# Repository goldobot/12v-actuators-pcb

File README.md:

# 12v-actuators-pcb
 Carte pour les actuateurs pneumatiques + capteur, moteurs brushless, répartition 12V et arrêt d'urgence du robot l'équipe Goldorak.

## Specs composants carte actionneurs 12V
- Fuse holder keystone 3557-2
- D2PAK for p-channel mosfet ( https://fr.rs-online.com/web/p/transistors-mosfet/7105014 )
- STM32 uC: STM32F042K6 MCU sur carte de développement compatible pinout Arduino Nano
- 3 esc modules on board 15A
- 2 esc 35 off-board signal + alim, connecteur imposé
- Capteurs de pression, double emprunte
- Passer le 12V au pont en H, connecteur imposé
- Entrée NTC 100k piston compresseur -> uC
- 3 sorties électrovannes + 1 sortie purge

## Specs générales
- Tout doit être en Français de préférence
- Passer de Batt\_12V\_P à PWR12 avec fusible + arrêt d'urgence
- 5V fourni en externe (a découpler) + common mode choke?
- Échéance du draft le dimanche 26 février

## Taille de la PCB

Estimation                 |  Comparaison avec une carte bancaire
:-------------------------:|:-------------------------:
  |  

_Dimensions en mm_

## Place dans l'architecture générale
Voir "Carte pneumatique", milieu-droite.

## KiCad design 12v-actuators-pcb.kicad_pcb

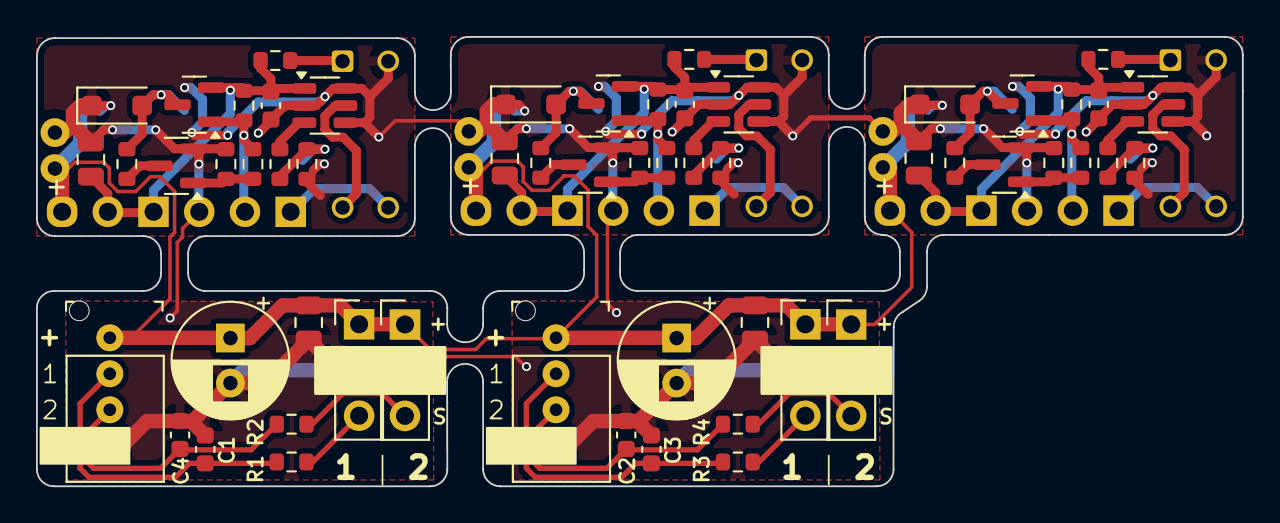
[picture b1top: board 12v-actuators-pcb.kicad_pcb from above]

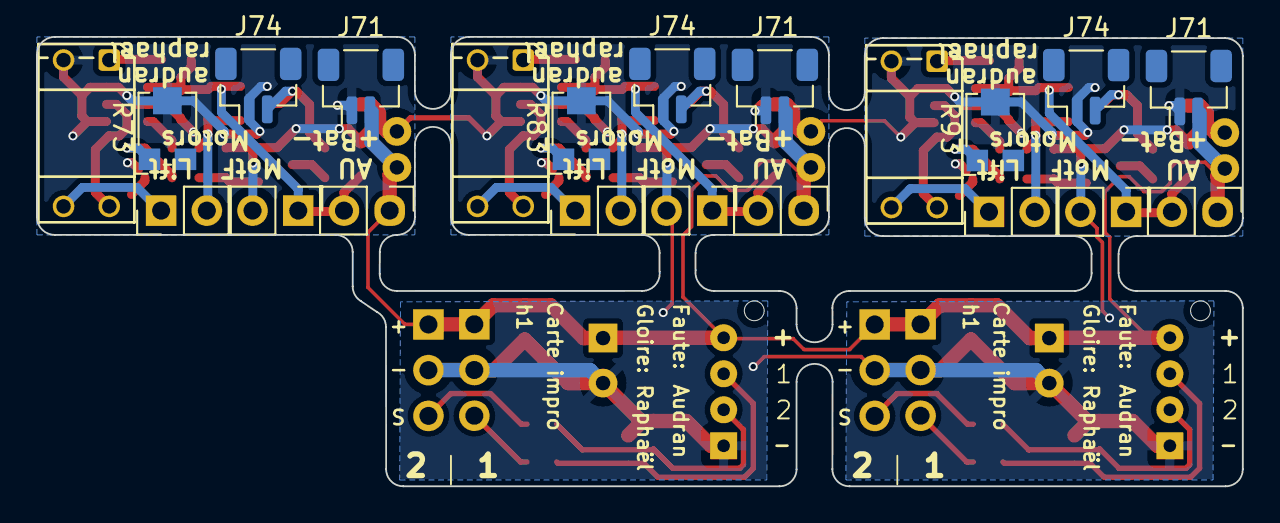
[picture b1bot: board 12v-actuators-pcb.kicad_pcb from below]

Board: 2 copper layers, 67.0 x 25.0 mm, 81 parts (24 on the bottom side), 12 nets.

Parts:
C1, C2, C3, C4: C_0603_1608Metric
C5, C7: C_0805_2012Metric
C6, C8: CP_Radial_D6.3mm_P2.50mm
C71, C81, C91: 220uF; C_Radial_D6.3mm_H11.0mm_P2.50mm
C72, C82, C92: 10uF; C_0805_2012Metric
C73, C83, C93: 100nF; C_0603_1608Metric
D71, D81, D91: RBR3MM40ATFTR; D_SOD-123F
J1, J1#2, J2, J2#2: PinHeader_1x03_P2.54mm_Vertical
J10, J11: PinHeader_1x04_P2.00mm_Vertical
J71, J71#2, J71#3, J74, J74#2, J74#3: 22-03-2021; JST_SH_BM02B-SRSS-TB_1x02-1MP_P1.00mm_Vertical
J72, J72#2, J72#3, J73, J73#2, J73#3, J75, J75#2, J75#3: 22-03-2021; PinHeader_1x02_P2.54mm_Vertical
Q71, Q81, Q91: ZXM61P03FTA; SOT-23
Q72, Q82, Q92: IRLML0040TRPBF; SOT-23
R1, R2, R3, R4: R_0603_1608Metric
R71, R81, R91: 33k; R_0603_1608Metric
R72, R82, R92: RC0603FR-0710KL; R_0603_1608Metric
R73, R83, R93: EVM2WSX80B54; Potentiometer_Bourns_TC33X_Vertical
R74, R78, R84, R88, R94, R98: RC0603FR-07330RL; R_0603_1608Metric
R75, R77, R85, R87, R95, R97: RC0603FR-07100KL; R_0603_1608Metric
R76, R86, R96: RC0603FR-071KL; R_0603_1608Metric
U71, U81, U91: TPL5110DDCT; SOT-23-6
U72, U82, U92: OPB620

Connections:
3L: C72.1, C73.1, C82.1, C83.1, C92.1, C93.1, J72.2, J72#2.2, J72#3.2, J75.1, J75#2.1, J75#3.1, Q71.2 (S), Q81.2 (S), Q91.2 (S), R74.1, R75.2, R84.1, R85.2, R94.1, R95.2, U71.1 (VDD), U81.1 (VDD), U91.1 (VDD)
/Mini-PAMI/BRAKE: J73.2, J73#2.2, J73#3.2, Q71.1 (G), Q81.1 (G), Q91.1 (G), R75.1, R76.2, R85.1, R86.2, R95.1, R96.2
/Mini-PAMI/MOTOR: D71.2, D81.2, D91.2, J74.2, J74#2.2, J74#3.2, Q71.3 (D), Q81.3 (D), Q91.3 (D), R78.2, R88.2, R98.2
/Mini-PAMI/OPB_A: R74.2, R84.2, R94.2, U72.1 (LED_A), U82.1 (LED_A), U92.1 (LED_A)
/Mini-PAMI/OPB_D: U71.5 (DRV), U72.4 (NPN_E), U81.5 (DRV), U82.4 (NPN_E), U91.5 (DRV), U92.4 (NPN_E)
/Mini-PAMI/OPB_S: J73.1, J73#2.1, J73#3.1, U72.3 (NPN_C), U82.3 (NPN_C), U92.3 (NPN_C)
BATT: C5.2, C6.1, C7.2, C8.1, C71.1, C81.1, C91.1, J1.1, J1#2.1, J2.1, J2#2.1, J10.1, J11.1, J71.2, J71#2.2, J71#3.2, J72.1, J72#2.1, J72#3.1
GND: C1.1, C2.1, C3.1, C4.1, C5.1, C6.2, C7.1, C8.2, C71.2, C72.2, C73.2, C81.2, C82.2, C83.2, C91.2, C92.2, C93.2, D71.1, D81.1, D91.1, J1.2, J1#2.2, J2.2, J2#2.2, J10.4, J11.4, J71.1, J71#2.1, J71#3.1, J74.1, J74#2.1, J74#3.1, J75.2, J75#2.2, J75#3.2, Q72.2 (S), Q82.2 (S), Q92.2 (S), R71.2, R73.2, R77.1, R81.2, R83.2, R87.1, R91.2, R93.2, R97.1, U71.2 (GND), U71.4 (DONE), U71.6 (EN/ONE_SHOT), U72.2 (LED_K), U81.2 (GND), U81.4 (DONE), U81.6 (EN/ONE_SHOT), U82.2 (LED_K), U91.2 (GND), U91.4 (DONE), U91.6 (EN/ONE_SHOT), U92.2 (LED_K)
unnamed: Q72.3 (D), Q82.3 (D), Q92.3 (D), R78.1, R88.1, R98.1
unnamed: Q72.1 (G), Q82.1 (G), Q92.1 (G), R76.1, R77.2, R86.1, R87.2, R96.1, R97.2
unnamed: R71.1, R72.1, R73.1, R81.1, R82.1, R83.1, R91.1, R92.1, R93.1
unnamed: R72.2, R82.2, R92.2, U71.3 (DELAY/M_DRV), U81.3 (DELAY/M_DRV), U91.3 (DELAY/M_DRV)

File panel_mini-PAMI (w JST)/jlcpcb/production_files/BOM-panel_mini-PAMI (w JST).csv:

Comment,Designator,Footprint,LCSC,Quantity
100nF,"C73,C83,C93",C_0603_1608Metric,C14663,3
ZXM61P03FTA,"Q71,Q81,Q91",SOT-23,C15127,3
RBR3MM40ATFTR,"D71,D81,D91",D_SOD-123F,C191023,3
IRLML0040TRPBF,"Q72,Q82,Q92",SOT-23,C20917,3
RC0603FR-071KL,"R76,R86,R96",R_0603_1608Metric,C21190,3
RC0603FR-07100KL,"R75,R85,R95",R_0603_1608Metric,C23192,3
R_0603_1608Metric,"R1,R2,R3,R4,R78,R88,R98",R_0603_1608Metric,C23345,7
RC0603FR-07330RL,"R74,R84,R94",R_0603_1608Metric,C25803,3
RC0603FR-0710KL,"R72,R77,R82,R87,R92,R97",R_0603_1608Metric,C25804,6
33k,"R71,R81,R91",R_0603_1608Metric,C4216,3
C_0805_2012Metric,"C5,C7,C72,C82,C92",C_0805_2012Metric,C440198,5
C_0603_1608Metric,"C1,C2,C3,C4",C_0603_1608Metric,C57112,4

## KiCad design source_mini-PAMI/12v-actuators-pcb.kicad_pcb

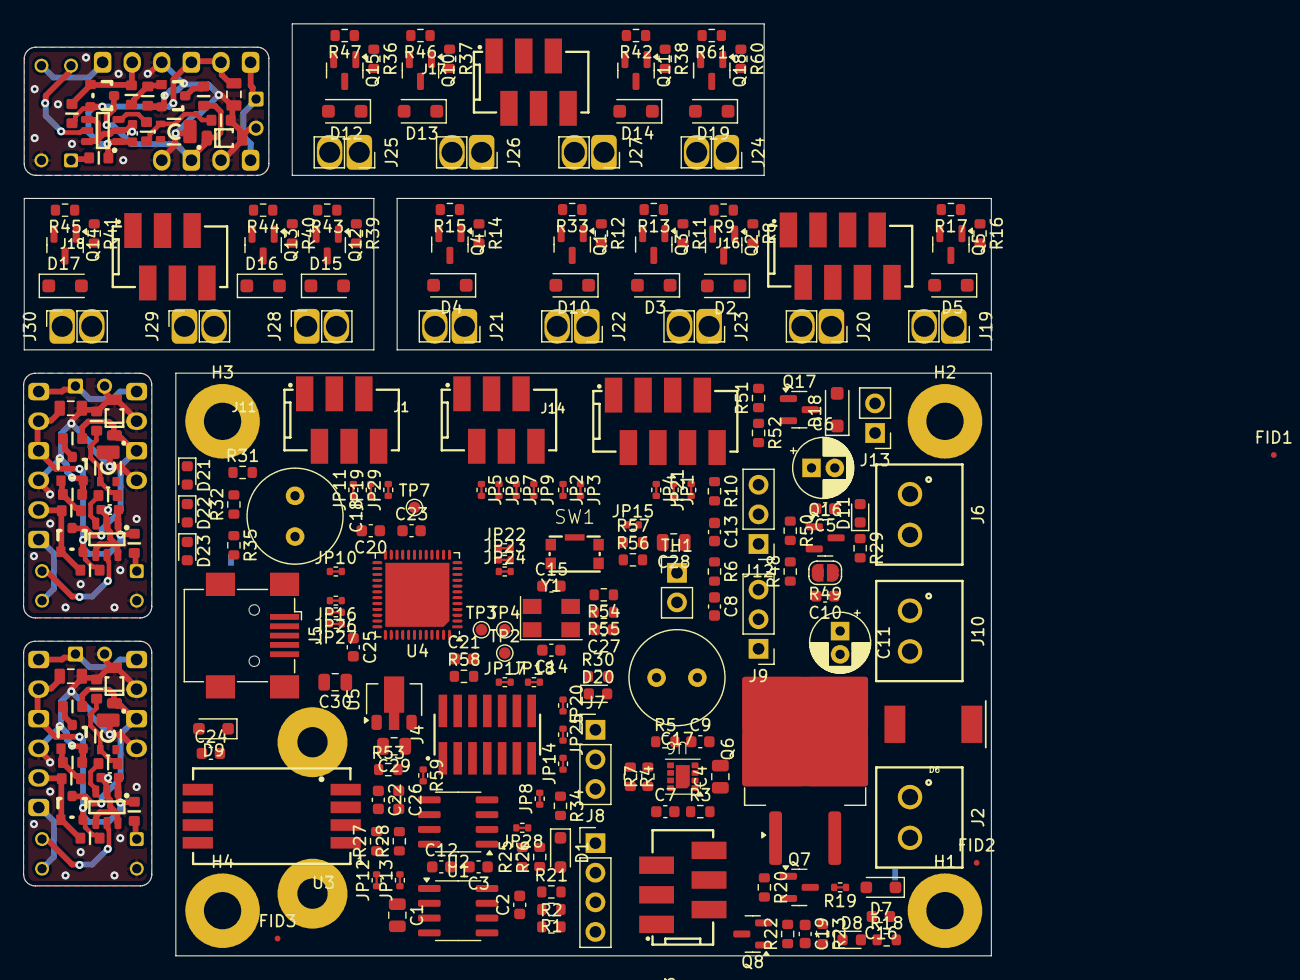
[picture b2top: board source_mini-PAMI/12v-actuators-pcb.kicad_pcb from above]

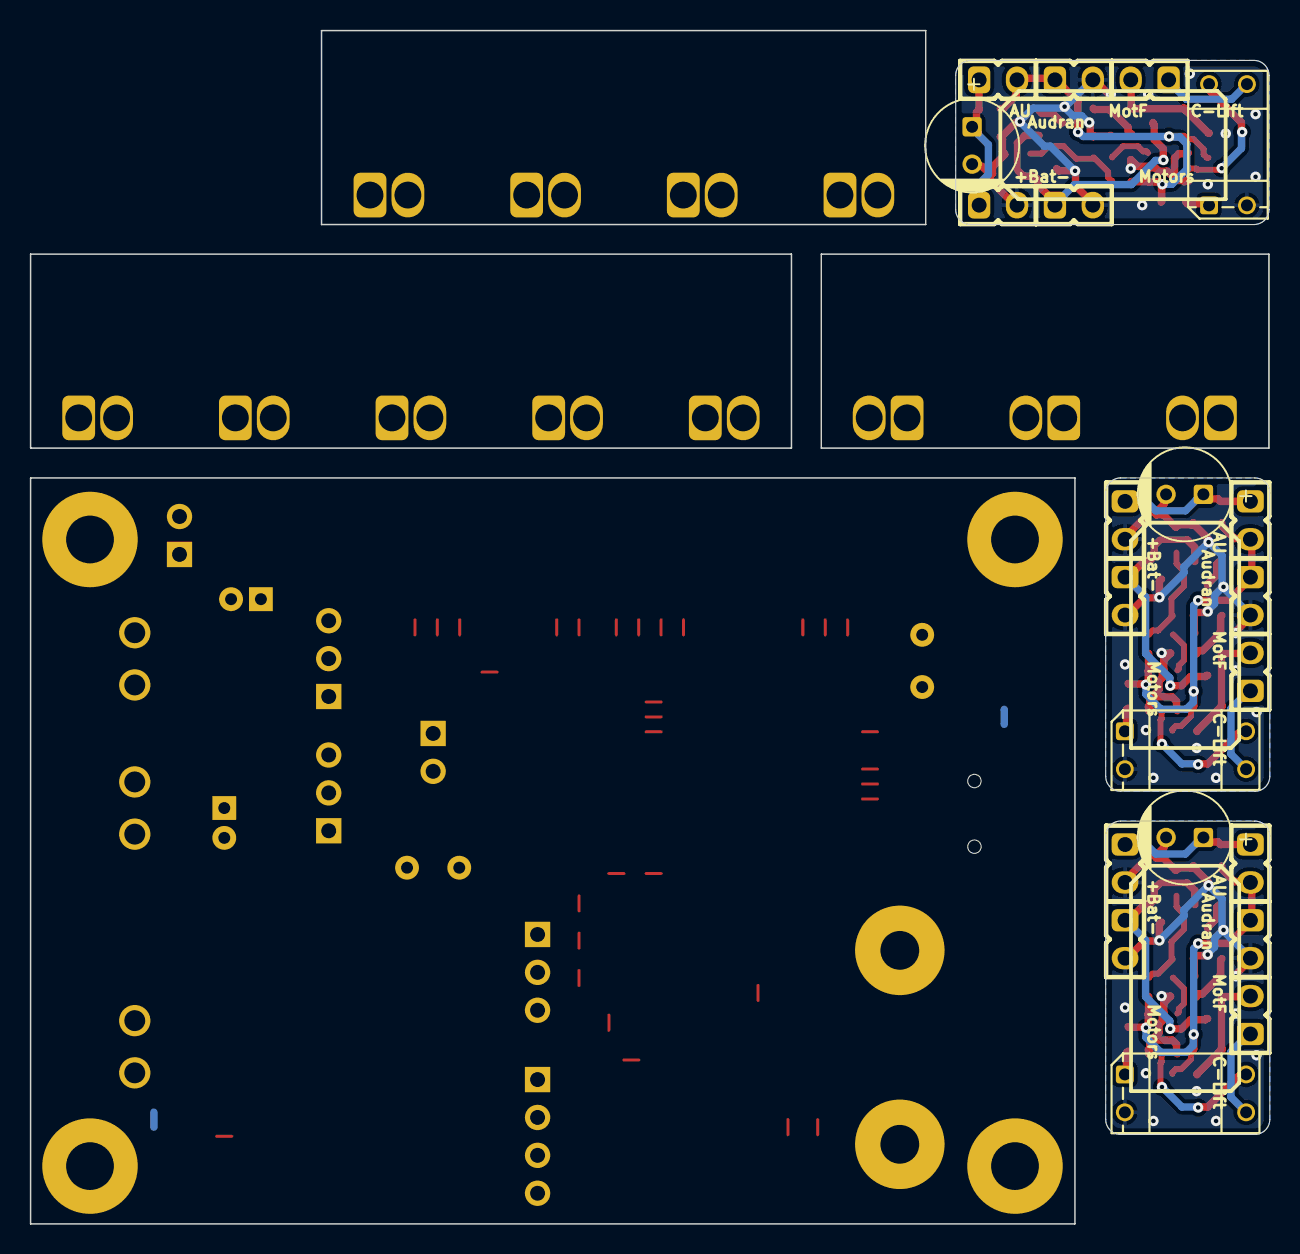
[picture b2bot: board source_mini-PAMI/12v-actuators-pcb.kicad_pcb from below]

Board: 2 copper layers, 83.1 x 80.0 mm, 273 parts (23 on the bottom side), 137 nets.

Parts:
C1, C4, C29, C30: 10uF; C_0805_2012Metric
C2: 1nF; C_0603_1608Metric
C3, C5, C10, C12, C16, C19, C21, C23, C27: 100nF; C_0603_1608Metric
C6, C11: 10uF; CP_Radial_D5.0mm_P2.00mm
C7: 430pF; C_0603_1608Metric
C8, C13: 470pF; C_0603_1608Metric
C9: 22uF; C_0603_1608Metric
C14, C15: 18pF; C_0603_1608Metric
C17, C18: 470uF; C_Radial_D8.0mm_H11.5mm_P3.50mm
C20, C25: 10nF; C_0603_1608Metric
C22, C26: 15nF; C_0603_1608Metric
C24: 220nF; C_0603_1608Metric
C28: 1uF; C_0805_2012Metric
C71, C81, C91: 220 uF; WCAP-ATG8_6.3x11x2.5x0.5
C72, C82, C92: 10uF; WCAP-CSGP_0805, 2x1.25x1.25
C73, C83, C93: 100nF; WCAP-CSGP_0603, 1.6x0.8x0.8
D1, D9: 1N5819WS; D_SOD-323_HandSoldering
D2, D3, D4, D5, D10, D12, D13, D14, D15, D16, D17, D18, D19: D_SOD-123F
D6: DO-214AB
D7: 14.6V; D_SOD-323_HandSoldering
D8, D11, D20, D21, D22, D23: LED; LED_0603_1608Metric
D71, D81, D91: RBR3MM40ATFTR; SOD-123FL
FID1, FID2, FID3: Fiducial; Fiducial_0.5mm_Mask1mm
H1, H2, H3, H4: MountingHole_Pad; MountingHole_3.2mm_M3_Pad
J1, J11, J17, J18: 690367280876; 690367280676
J2: 3.5mm WR-TBL; 691321100002
J3: 690367280676
J4: STLINK; SAMTEC_FTSH-107-01-L-DV-K
J5: USB_B_Mini; USB_Mini-B_Wuerth_65100516121_Horizontal
J6, J10: ESC_35_1_P; 691321100002
J7: RGBA_LEDs; PinHeader_1x03_P2.54mm_Vertical
J8: CAN; PinHeader_1x04_P2.54mm_Vertical
J9: ESC_35_1_S; PinHeader_1x03_P2.54mm_Vertical
J12: ESC_35_2_S; PinHeader_1x03_P2.54mm_Vertical
J13: Alim Pompe; PinHeader_1x02_P2.54mm_Vertical
J14, J16: 690367280876
J19, J20, J21, J22, J23, J24, J25, J26, J27, J28, J29, J30: Alim EV; PinSocket_1x02_P2.54mm_Vertical_widePad
J71, J72, J73, J78, J79, J81, J82, J83, J88, J89, J91, J92, J93, J98, J99: 22-03-2021; Conn_22-03-2021
JP1, JP2, JP3, JP4, JP5, JP6, JP7, JP8, JP9, JP10, JP11, JP12, JP13, JP14, JP15, JP16, JP17, JP18, JP19, JP20, JP21, JP22, JP23, JP24, JP25, JP26, JP27, JP28, JP29: SolderJumper_2_Bridged; R_0402_1005Metric_jumperClosed
Q1, Q2, Q3, Q4, Q5, Q10, Q11, Q12, Q13, Q14, Q15, Q16, Q17, Q18: G2302; SOT-23
Q6: SUM110P06-08L; TO-263-2
Q7, Q8: 2N7002; SOT-23
Q72, Q82, Q92: ZXM61P03FTA; SOT-23
Q73, Q83, Q93: IRLML0040TRPBF; SOT-23
R1, R2: 68; R_0603_1608Metric
R3, R9, R13, R15, R17, R18, R21, R22, R23, R25, R26, R27, R28, R29, R33, R34, R42, R43, R44, R45, R46, R47, R48, R52, R57, R58, R61: 10k; R_0603_1608Metric
R4, R7, R54, R55: 100k; R_0603_1608Metric
R5: 523k; R_0603_1608Metric
R6, R10, R50, R53, R56: 22; R_0603_1608Metric
R8, R11, R12, R14, R16, R31, R32, R35, R36, R37, R38, R39, R40, R41, R51, R60: 1k; R_0603_1608Metric
R19, R59: 0; R_0402_1005Metric_jumperClosed
R20, R30: 4.7k; R_0603_1608Metric
R24, R62: 0; NetTie-2_SMD_Pad0.5mm
R49: 0; SolderJumper-2_P1.3mm_Open_RoundedPad1.0x1.5mm
R71, R81, R91: RC0603FR-0710KL; RESC1608X06N
R72, R82, R92: RESC1608X06N
R73, R83, R93: EVM2WSX80B54; TRIM_PANASONIC_EVM-2W
R75, R79, R85, R89, R95, R99: RC0603FR-07100KL; RESC1608X06N
R76, R77, R86, R87, R96, R97: RC0603FR-07330RL; RESC1608X06N
R78, R88, R98: RC0603FR-071KL; RESC1608X06N
SW1: 435431019840
TH1: NTC; PinHeader_1x02_P2.54mm_Vertical
TP2, TP3, TP4, TP7: TestPoint_Small; TestPoint_Pad_D1.0mm
U1: MCP2551-I-SN; SOIC-8_3.9x4.9mm_P1.27mm
U2: TCA9517DR; SOIC-8_3.9x4.9mm_P1.27mm
U3: WSEN-PDUS; WSEN-PDUS_2513130810X01
U4: STM32G474CEUx; QFN-48-1EP_7x7mm_P0.5mm_EP5.5x5.5mm
U5: AMS1117-3.3; SOT-89-3
U6: TPS82130; MicroSiP
U71, U81, U91: TPL5110DDCT; SOT23_95P280X145-6N
U72, U82, U92: OPB620
Y1: 16 MHz; Crystal_SMD_5032-4Pin_5.0x3.2mm

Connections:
3L: Q72.2 (S), Q82.2 (S), Q92.2 (S)
+3.3V: C3.1, C20.1, C21.1, C23.1, C25.1, C30.1, J4.3, R21.1, R25.1, R26.1, R54.1, R55.1, R57.2, U2.1 (VCCA), U4.21 (VDDA), U4.23 (VDD), U4.35 (VDD), U4.48 (VDD), U5.2 (VO)
+5VL: C1.2, C12.1, C24.1, C29.1, D1.1 (K), D9.1 (K), R27.1, R28.1, R34.2, R59.1, U1.3 (VDD), U2.8 (VCCB), U3.5 (VDD), U5.3 (VI)
+5VP: C9.1, D20.2 (A), J7.1, R4.1, R5.2, U6.4 (VOUT), U6.5 (VOUT)
/5L: D1.2 (A), J3.3, J8.1
/5V_USB: D9.2 (A), J5.1 (VBUS)
/AU_STATUS: JP25.2 (B), Q8.3 (D), R21.2
/Actionneurs/12V_EV1: D2.2 (A), J20.2, Q2.3 (D)
/Actionneurs/12V_EV2: D3.2 (A), J23.2, Q3.3 (D)
/Actionneurs/12V_EV3: D4.2 (A), J21.2, Q4.3 (D)
/Actionneurs/12V_EV4: D10.2 (A), J22.2, Q1.3 (D)
/Actionneurs/12V_EV5: D19.2 (A), J24.2, Q18.3 (D)
/Actionneurs/12V_EV6: D12.2 (A), J25.2, Q15.3 (D)
/Actionneurs/12V_EV7: D13.2 (A), J26.2, Q10.3 (D)
/Actionneurs/12V_EV8: D14.2 (A), J27.2, Q11.3 (D)
/Actionneurs/12V_EV9: D15.2 (A), J28.2, Q12.3 (D)
/Actionneurs/12V_EV10: D16.2 (A), J29.2, Q13.3 (D)
/Actionneurs/12V_EV11: D17.2 (A), J30.2, Q14.3 (D)
/Actionneurs/12V_EVP: D5.2 (A), J19.2, Q5.3 (D)
/Actionneurs/12V_VAC: D18.2 (A), J13.2, Q17.3 (D)
/Alim et Arrêt d'urgence/SW_AU/2: C19.1, D8.2 (A), Q7.1 (G), Q8.1 (G), R20.2, R22.2
/CANH: J8.3, R1.1, U1.7 (CANH)
/CANL: J8.4, R2.2, U1.6 (CANL)
/CAN_RX: JP12.1 (A), U1.4 (RXD)
/CAN_TX: JP13.1 (A), U1.1 (TXD)
/DATA_LED: J7.2, JP20.2 (B)
/DS_COMP: JP24.2 (B), R6.1
/DS_TURB: JP23.2 (B), R10.1, R50.1
/EV_1: J14.3, J16.3, JP2.1 (A), R8.2
/EV_2: J14.4, J16.4, JP3.1 (A), R11.2
/EV_3: J14.5, J16.5, JP4.1 (A), R14.2
/EV_4: J14.6, J16.6, JP1.1 (A), R12.2
/EV_5: J1.3, J17.3, JP5.1 (A), R60.2
/EV_6: J1.4, J17.4, JP6.1 (A), R36.2
/EV_7: J1.5, J17.5, JP7.1 (A), R37.2
/EV_8: J1.6, J17.6, JP9.1 (A), R38.2
/EV_9: J11.3, J18.3, JP10.1 (A), R39.2
/EV_10: J11.4, J18.4, JP11.1 (A), R40.2
/EV_11: J11.5, J18.5, JP19.2 (B), R41.2
/EV_12: J11.6, JP29.2 (B)
/EV_P: J14.8, J16.8, JP21.2 (B), R16.2
/LED_EN: JP14.1 (A), R3.2, R34.1, U6.1 (EN)
/MCU et capteurs/AU_STATUS_J: JP25.1 (A), U4.47 (PB9)
/MCU et capteurs/A_PRES: C26.1, JP16.2 (B), R53.2
/MCU et capteurs/A_PRES_J: JP16.1 (A), U4.31 (PA9)
/MCU et capteurs/A_TEMP: C28.2, JP15.2 (B), R56.2
/MCU et capteurs/A_TEMP_J: JP15.1 (A), U4.9 (PA1)
/MCU et capteurs/BOOT0: R58.1, U4.46 (PB8)
/MCU et capteurs/CAN_RX_J: JP12.2 (B), U4.43 (PB5)
/MCU et capteurs/CAN_TX_J: JP13.2 (B), U4.44 (PB6)
/MCU et capteurs/DATA_LED_J: JP20.1 (A), U4.8 (PA0)
/MCU et capteurs/DS_COMP_J: JP24.1 (A), U4.10 (PA2)
/MCU et capteurs/DS_TURB_J: JP23.1 (A), U4.11 (PA3)
/MCU et capteurs/EV_1_J: JP2.2 (B), U4.17 (PB0)
/MCU et capteurs/EV_2_J: JP3.2 (B), U4.16 (PC4)
/MCU et capteurs/EV_3_J: JP4.2 (B), U4.15 (PA7)
/MCU et capteurs/EV_4_J: JP1.2 (B), U4.14 (PA6)
/MCU et capteurs/EV_5_J: JP5.2 (B), U4.24 (PB11)
/MCU et capteurs/EV_6_J: JP6.2 (B), U4.22 (PB10)
/MCU et capteurs/EV_7_J: JP7.2 (B), U4.19 (PB2)
/MCU et capteurs/EV_8_J: JP9.2 (B), U4.18 (PB1)
/MCU et capteurs/EV_9_J: JP10.2 (B), U4.28 (PB15)
/MCU et capteurs/EV_10_J: JP11.2 (B), U4.27 (PB14)
/MCU et capteurs/EV_11_J: JP19.1 (A), U4.26 (PB13)
/MCU et capteurs/EV_12_J: JP29.1 (A), U4.25 (PB12)
/MCU et capteurs/EV_P_J: JP21.1 (A), U4.13 (PA5)
/MCU et capteurs/LED_DBG_1: D21.2 (A), U4.29 (PC6)
/MCU et capteurs/LED_DBG_2: D22.2 (A), U4.30 (PA8)
/MCU et capteurs/LED_DBG_3: D23.2 (A), U4.32 (PA10)
/MCU et capteurs/LED_EN_J: JP14.2 (B), U4.42 (PB4)
/MCU et capteurs/NRST: J4.12, R57.1, SW1.1, SW1.4, U4.7 (PG10)
/MCU et capteurs/OSC0: C14.2, U4.5 (PF0), Y1.1
/MCU et capteurs/OSC1: C15.2, U4.6 (PF1), Y1.3
/MCU et capteurs/SCL: JP28.2 (B), R25.2, U2.2 (SCLA)
/MCU et capteurs/SCL_5: R28.2, U2.7 (SCLB), U3.1 (SCL)
/MCU et capteurs/SCL_J: JP28.1 (A), U4.38 (PA15)
/MCU et capteurs/SDA: JP8.1 (A), R26.2, U2.3 (SDAA)
/MCU et capteurs/SDA_5: R27.2, U2.6 (SDAB), U3.2 (SDA)
/MCU et capteurs/SDA_J: JP8.2 (B), U4.45 (PB7)
/MCU et capteurs/SWDIO: J4.4, U4.36 (PA13)
/MCU et capteurs/SWO: J4.8, U4.41 (PB3)
/MCU et capteurs/SWTCK: J4.6, U4.37 (PA14)
/MCU et capteurs/TP2: TP2.1, U4.2 (PC13)
/MCU et capteurs/TP3: TP3.1, U4.3 (PC14)
/MCU et capteurs/TP4: TP4.1, U4.4 (PC15)
/MCU et capteurs/USB_DN_J: JP26.1 (A), U4.33 (PA11)
/MCU et capteurs/USB_DP_J: JP27.1 (A), U4.34 (PA12)
/MCU et capteurs/VAC_J: JP22.1 (A), U4.12 (PA4)
/MCU et capteurs/VCP_RX: J4.13, JP18.2 (B)
/MCU et capteurs/VCP_RX_J: JP18.1 (A), U4.40 (PC11)
/MCU et capteurs/VCP_TX: J4.14, JP17.2 (B)
/MCU et capteurs/VCP_TX_J: JP17.1 (A), U4.39 (PC10)
/MCU et capteurs/VREF_uC: TP7.1, U4.20 (VREF+)
/PWR_12V: C5.2, C6.1, C10.2, C11.1, C17.1, C18.1, D2.1 (K), D3.1 (K), D4.1 (K), D6.2 (A), D10.1 (K), D11.2 (A), D12.1 (K), D13.1 (K), D14.1 (K), D15.1 (K), D16.1 (K), D17.1 (K), D18.1 (K), D19.1 (K), J1.1, J6.1, J10.1, J11.1, J13.1, J14.1, J16.1, J17.1, J18.1, J20.1, J21.1, J22.1, J23.1, J24.1, J25.1, J26.1, J27.1, J28.1, J29.1, J30.1, Q6.2 (D)
/SW_AU: J3.5, R20.1
/USB_DN: J5.2 (D-), JP26.2 (B)
/USB_DP: J5.3 (D+), JP27.2 (B)
/VAC: JP22.2 (B), R51.2
/VBATT_12V: C4.1, C16.1, D5.1 (K), D6.1 (K), D7.1 (K), J2.1, J14.7, J16.7, J19.1, Q6.3 (S), R18.2, U6.2 (VIN)
/mini-pami/BRAKE: Q72.1 (G), Q82.1 (G), Q92.1 (G)
/mini-pami/MOTOR: Q72.3 (D), Q82.3 (D), Q92.3 (D)
GND: C1.1, C2.2, C3.2, C8.2, C12.2, C13.2, C14.1, C15.1, C19.2, C20.2, C21.2, C22.2, C23.2, C24.2, C25.2, C26.2, C27.1, C28.1, C29.2, C30.2, C71.2, C72.2, C73.2, C81.2, C82.2, C83.2, C91.2, C92.2, C93.2, D71.1, D81.1, D91.1, H1.1, H2.1, H3.1, H4.1, J3.2, J4.5, J4.7, J4.11, J5.5 (GND), J5.6 (Shield), J8.2, J9.1, J12.1, J72.2, J78.2, J79.2, J82.2, J88.2, J89.2, J92.2, J98.2, J99.2, Q73.2 (S), Q83.2 (S), Q93.2 (S), R22.1, R23.2, R24.2, R31.2, R32.2, R35.2, R58.2, R62.2, R72.2, R73.2, R79.1, R82.2, R83.2, R89.1, R92.2, R93.2, R99.1, SW1.2, SW1.3, SW1.SH, TH1.2, U1.2 (VSS), U1.8 (Rs), U2.4 (GND), U3.3 (GND), U4.49 (VSS), U5.1 (GND), U71.2 (GND), U71.4 (DONE), U71.6 (EN/ONE_SHOT), U72.2 (LED_K), U81.2 (GND), U81.4 (DONE), U81.6 (EN/ONE_SHOT), U82.2 (LED_K), U91.2 (GND), U91.4 (DONE), U91.6 (EN/ONE_SHOT), U92.2 (LED_K), Y1.2, Y1.4
GNDPWR: C4.2, C5.1, C6.2, C7.2, C9.2, C10.1, C11.2, C17.2, C18.2, J1.2, J2.2, J7.3, J10.2, J11.2, J14.2, J16.2, J17.2, J18.2, Q1.2 (S), Q2.2 (S), Q3.2 (S), Q4.2 (S), Q5.2 (S), Q7.2 (S), Q8.2 (S), Q10.2 (S), Q11.2 (S), Q12.2 (S), Q13.2 (S), Q14.2 (S), Q15.2 (S), Q16.2 (S), Q17.2 (S), Q18.2 (S), R3.1, R7.1, R9.2, R13.2, R15.2, R17.2, R24.1, R30.2, R33.2, R42.2, R43.2, R44.2, R45.2, R46.2, R47.2, R48.1, R49.2 (B), R52.2, R61.2, R62.1, U6.3 (GND), U6.9 (GND)
unnamed: C2.1, R1.2, R2.1
unnamed: C27.2, R54.2, R55.2, R56.1, TH1.1
unnamed: C16.2, D7.2 (A), Q6.1 (G), R18.1, R19.1
unnamed: D8.1 (K), R23.1
unnamed: D11.1 (K), R29.1
unnamed: D20.1 (K), R30.1
unnamed: D21.1 (K), R31.1
unnamed: D22.1 (K), R32.1
unnamed: D23.1 (K), R35.1
unnamed: J6.2, Q16.3 (D), R29.2, R49.1 (A)
unnamed: C8.1, J9.3, R6.2
unnamed: C13.1, J12.3, R10.2
unnamed: Q1.1 (G), R12.1, R33.1
unnamed: Q2.1 (G), R8.1, R9.1
unnamed: Q3.1 (G), R11.1, R13.1, R78.1, R79.2, R88.1, R89.2, R98.1, R99.2
unnamed: Q4.1 (G), R14.1, R15.1
unnamed: Q5.1 (G), R16.1, R17.1
unnamed: Q7.3 (D), R19.2
unnamed: Q10.1 (G), R37.1, R46.1
unnamed: Q11.1 (G), R38.1, R42.1
unnamed: Q12.1 (G), R39.1, R43.1
unnamed: Q13.1 (G), R40.1, R44.1
unnamed: Q14.1 (G), R41.1, R45.1
unnamed: Q15.1 (G), R36.1, R47.1
unnamed: Q16.1 (G), R48.2, R50.2
unnamed: Q17.1 (G), R51.1, R52.1
unnamed: Q18.1 (G), R60.1, R61.1
unnamed: Q73.3 (D), Q93.3 (D)
unnamed: Q73.1 (G), Q93.1 (G)
unnamed: R59.2, U2.5 (EN)
unnamed: C22.1, R53.1, U3.4 (VOUT)
unnamed: R5.1, R7.2, U6.6 (FB)
unnamed: R4.2, U6.7 (PG)
unnamed: C7.1, U6.8 (SS/TR)

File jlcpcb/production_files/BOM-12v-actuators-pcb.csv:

Comment,Designator,Footprint,LCSC,Quantity
STM32G474CEUx,U4,QFN-48-1EP_7x7mm_P0.5mm_EP5.5x5.5mm,C1235412,1
TPL5110DDCT,"U71,U81,U91",SOT-23-6,C125830,3
16 MHz,Y1,Crystal_SMD_3225-4Pin_3.2x2.5mm,C13738,1
100nF,"C10,C12,C16,C19,C21,C23,C24,C27,C3,C36,C37,C5,C73,C83,C93",C_0603_1608Metric,C14663,15
ZXM61P03FTA,"Q71,Q81,Q91",SOT-23,C15127,3
1nF,C2,C_0603_1608Metric,C1588,1
470pF,"C13,C7,C8",C_0603_1608Metric,C1620,3
15pF,"C14,C15",C_0603_1608Metric,C1647,2
TCA9517DR,U2,SOIC-8_3.9x4.9mm_P1.27mm,C182421,1
1N5819WS,"D1,D24,D9",D_SOD-323_HandSoldering,C191023,3
G2302,"Q1,Q10,Q11,Q12,Q13,Q14,Q15,Q16,Q17,Q18,Q19,Q2,Q3,Q4,Q5,Q7,Q72,Q8,Q82,Q92",SOT-23,C20917,20
1k,"R11,R12,R14,R16,R23,R31,R32,R35,R36,R37,R38,R39,R40,R41,R51,R60,R76,R8,R86,R96",R_0603_1608Metric,C21190,20
13k,R64,R_0603_1608Metric,C22797,1
LED,"D11,D20,D21,D8",LED_0603_1608Metric,C2286,4
LED,"D22,D23",LED_0603_1608Metric,C2290,2
RC0603FR-07330RL,"R74,R78,R84,R88,R94,R98",R_0603_1608Metric,C23138,6
4.7k,R30,R_0603_1608Metric,C23162,1
510k,R5,R_0603_1608Metric,C23192,1
22,"R10,R50,R53,R56,R6,R66",R_0603_1608Metric,C23345,6
100k,"R4,R54,R55,R7,R75,R77,R85,R87,R95,R97",R_0603_1608Metric,C25803,10
10k,"R13,R15,R17,R18,R21,R22,R25,R26,R27,R28,R29,R3,R33,R42,R43,R44,R45,R46,R47,R48,R52,R57,R58,R61,R65,R72,R82,R9,R92",R_0603_1608Metric,C25804,29
1uF,"C28,C31",C_0805_2012Metric,C28323,2
SW_Push,SW2,SW_Push_1P1T_XKB_TS-1187A,C318884,1
RS3J R6,D6,DO-214AB,C330388,1
33k,"R71,R81,R91",R_0603_1608Metric,C4216,3
SUM110P06-08L,Q6,TO-263-2,C435954,1
10uF,"C1,C29,C30,C32,C33,C34,C35,C4,C72,C82,C92",C_0805_2012Metric,C440198,11
22uF,C9,C_0805_2012Metric,C45783,1
TPS82130,U6,MicroSiP,C473914,1
10nF,"C20,C22,C25,C26",C_0603_1608Metric,C57112,4
MM3Z15VST1G,D7,D_SOD-323_HandSoldering,C603316,1
AMS1117-3.3,U5,SOT-223-3_TabPin2,C6186,1
65100516121,J5,USB_Mini-B_Wuerth_65100516121_Horizontal,C720611,1
MCP2551-I-SN,U1,SOIC-8_3.9x4.9mm_P1.27mm,C7376,1
1N4148W,"D10,D12,D13,D14,D15,D16,D17,D18,D19,D2,D3,D4,D5,D71,D81,D91",D_SOD-123F,C81598,16

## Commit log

2023-02-26 Project start
2023-02-26 Add 3.5mm header datasheet
2023-02-26 Ajout d'une comparaison de taille dans le README
2023-03-05 WIP: schematic begun
2023-03-11 WIP: Arrêt d'urgence
2023-03-14 Schéma AU fait + ESC + électrovannes débuté
2023-03-22 Schematics mostly done, EV and ESC pins to validate with @MGMaximusk
2023-03-22 Ajout du logo de l'équipe
2023-03-26 Reorganize and finish schematic, assign footprints
2023-03-27 Correct CAN interface, add some filtering on sensors + add LCD board power connector
2023-03-27 Few details -> add filtering on 35A ESC signals + 3.3V capa ...
2023-03-28 Schematics finished, reanotated sch
2023-03-29 First placement draft
2023-04-01 Update schematic pinout for LED_EN + Add mechanical constraints to PCB layout
2023-04-01 Update PDF output
2023-04-02 add pinout.txt
2023-04-02 New PCB reorganisation around mechanical constraints
2023-04-04 Before making power planes
    Signal routing done. Added I2C level shifter in schematics.
2023-04-05 PCB finished
2023-04-05 Update picture
2023-04-05 reprise des plans et petite correction diverse
2023-04-05 oups, il manquait les fichiers proj et pcb
2023-04-05 Regenerate interactive BOM
2023-04-05 Update board 3D STEP file
2023-04-05 Update board 3D STEP files
2025-03-18 CDR 2025 version WIP
2025-03-20 Simplification arborescence schema, correction duplicate designator TODO: connect floating signal on MCU sheet, update routing, split the board in two
2025-03-24 Correction de signaux non connectes, ajout de connecteur manquant, mise en forme du TOP
2025-03-25 split des cartes
    Todo: sync routage et ajout trou de fixation
2025-03-25 ajout d'une lib projet et synchro PCB
2025-03-25 optimisation empreinte passif (TODO fp diode), TODO ajouter LED temoin diverse, groupement sur PCB des nouveaux composant
2025-03-26 placement en cours, remplacement diode schotcky, customisation empreinte capteur pression, suppression R pour les signaux figé du uC (SW, BOOT, etc). TODO avancer placement, ajouter LED
2025-03-27 placement composant (carte distributeur)
2025-03-27 ajout regle routage JLCPCB, fin placement grossier et debut reassignation. ajout de led temoin, homogeinisation empreinte passif et remplacement 0ohm par empreintre jumper PCB 0402.
2025-03-27 fin du placement et reassignation des pins uC
2025-03-28 ajout regle routage (oubli)
2025-03-28 ajout empreinte 0402
2025-03-28 nettoyage dossier et assignation de ref JLCPCB
2025-03-28 Correction orientation conn alim
2025-03-31 debut du tracee des pistes (et modification de l'empreinte R_0402_1005Metric_jumperClosed.kicad_mod pour que le DRC accepte de la router
2025-04-01 Minor adjust before routing
2025-04-04 Routing 40%
2025-04-05 Routing 41%
2025-04-07 fin tracer piste et plan carte principale - mise a jour regle ERC sur la base de la carte Pneuma 2023 et alim 2020 - no ERC
2025-04-07 debut routage carte peripherique
2025-04-08 fin routage piste et plan carte annexe + board shape - no ERC TODO: serigraphie, ERC, pcb mini-PAMI, jlcpcb prod file
2025-04-08 added generic JLCPCB switch for reset and gnd netTie
2025-04-08 debut placement serigraphie et ajout fichier mini-pami
2025-04-09 ajout capa sur carte peripherique, fin placement serigraphie top
2025-04-09 ajout serigraphie bottom et DRC revu (reste acceptable)
2025-04-14 WIP ajout des carte Mini-PAMI au routage (todo: finir routage, repeter, associer ref JLCPCB, enregistrer empreinte OPB620 et TRIMM)
2025-04-15 serigraphie et duplication des PCB mini-PAMI, panelisation. (TODO: piste inter-pcb, assign LCSC)
2025-04-16 corrrection footprint trim, ajout R64, config JLCPCB ASSY, fin panelisation (TODO: revue et cmd)
2025-04-21 mise à jour du schema après la coupe de belgique
    - modification du circuit d'AU (SW_AU 24V->3.3V)
    - modification du pinout de J3: ajout du CAN (suppression de J8) et du RST_EXT
    - ajout d'un circuit de reset externe (configurable via 3-jumper)
    - ajout d'un connecteur dédié pour un bouton reset externe
    - ajout d'un debounce sur le switch reset
    - mise à jour du routage et serigraphie
2025-04-22 Maj crystal et connection therminque DC-DC
2025-04-22 commande du PCB
2025-04-23 mise à jour de l'origine de grille (pour genered STEP)
2025-05-11 PAMI seuls + ajout carte impro
2025-05-12 correction after Raphael routing
    aligned board,
    individualized designator for Assy
    removed via in-pad
    updated silkscreen
    note: pcb file will be moved to branch 2025 to prepare production files
2025-05-12 Added file for mini-PAMI panel with JST
2025-05-18 ajout note patch VREF
2025-06-02 ajout note de debug
2025-06-12 added Patches
